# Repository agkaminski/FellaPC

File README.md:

# FellaPC

All-in-keyboard 6502 based PC with built-in BASIC interpreter.

Features:

- BASIC interpreter,
- 6502/65C02/W65C02S CPU @1.8432 MHz,
- 32 KiB of ROM, 24 KiB of static RAM,
- 640x480@60Hz VGA adapter with character generator (80x60 black and white text mode only),
- 6522 VIA for onboard control, I2C memory and user port,
- 2 UARTs (USB-C and RS-232),
- 68 or 63 button mechanical keyboard,
- edge connector expansion port,
- powered via USB-C port.

## Memory map

[Memory map](memmap.md)

## BASIC

FellaPC provides BASIC language subset (partially inspired by C64 BASIC).

### Program editing

Simple line editor is provided, code is entered line by line. To insert a new line or
overwrite existing line type in the line number followed by the code.

Example

```
10 FOR I = 0 TO 10
20 PRINT I
30 NEXT I
```

Let's say we want to change line number 20 to print a square of I insted. To do this
simply type in a new version of this line:

```
20 PRINT I*I
```

The program will be updated:

```
LIST

10 FOR I = 0 TO 10
20 PRINT I*I
30 NEXT I

Ready
```

### Commands

Following commands are supported:

#### PRINT

Print out to the screen.

Syntax examples:

```
PRINT "String"
PRINT "String", variable
PRINT "String"; variable
PRINT variable
PRINT var1, var2
```

#### INPUT

Prompt user for input, real numbers only.

Syntax examples:

```
INPUT var
INPUT "Prompt", var
```

#### FOR, TO, STEP, NEXT

Used for loops. Intelacing and infinite loop nesting are supported.

Syntax example:

```
10 FOR VAR=0 TO 10 STEP 2
20 PRINT I
30 NEXT I
```

Above loop will output:

```
0
2
4
6
8
```

#### GOTO

Jump to the line in the code.

Syntax example:

```
10 GOTO 30
20 PRINT "foo"
30 PRINT "bar"
```

Above code will output only `bar`, as `foo` has been skipped by `goto`.

#### GOSUB, RETURN

Similar to GOTO, but allows returning back from the destination of jump via `RETURN`.
Return address (line after `GOSUB`) is placed on the return stack. There is no limit
on the stack depth (apart from the computer memory capacity).

Syntax example:

```
10 GOSUB 200
20 PRINT "bar"
30 END
200 PRINT "foo"
210 RETURN
```

Folowing code will output:

```
foo
bar
```

#### IF, THEN, ELSE

Conditional execution.

Syntax example:

```
var = 5
10 IF var > 10 THEN 100 ELSE 200
100 PRINT "foo"
200 PRINT "bar"
```

Above code will only output `bar`, as var is not greater than 10.

#### CLEAR

Clear the screen and return cursor to the home position.

#### END

End program execution, return the interactive mode.

#### RUN

Starts execution of the program. Can be used in the interactive mode only.

#### LIST

Displays program. Can be used in the interactive mode only.

#### SAVE

Stores the program on the non-volatile memory. Can be used in the interactive mode only.

#### LOAD

Loads the program from the non-volatile memory. Can be used in the interactive mode only.

#### ABS()

Return absolute value.

Syntax example:

```
10 PRINT ABS(-5)
20 PRINT ABS(5)
```

This program will output:

```
5
5
```

#### FRE

Pseudo-variable. Return available BASIC memory in bytes.

#### INT()

Returns integer part of the real number.

Syntax example

```
PRINT INT(3.1412)
```

Will output `3`.

#### RND

Pseudo-variable. Return a random real number in the range of <0, 1).

#### PEEK(), POKE()

Functions that allow direct reading and modification of the computer memory.

Syntax examples:

```
PRINT PEEK(100)
```

Displays value of the memory at address 100.

```
POKE(100, 42)
```

Stores 42 at the address 100.

#### Operators

Following operators are supported:

```
( ) * + , - / ; < = > <= >= AND NOT OR
```

#### Variables

Variables are declared on the first use:

```
a = 5
var = 42
```

## Limitations

Applies to rev A, rev B:

All limitations in the firmware come from the limited size of the ROM space and
poor performance of the CC65 C compiler. 16 KB of program memory was thought to be
just enought to fit a full BASIC interpreter implementation. Alas, CC65 does not optimize
almost at all for the code size. 6502 is also infamous of not playing nice with the
C language. There was much struggle at the end of the development with the ROM space
running out - so some features were removed or abandoned and some functions has been
rewritten in assembled instead (which provides huge savings). It was deciced against
writing the BASIC interpreter itself in the assembler, in hope to reuse it in the future
project, with its portability in mind. Writing the whole firmware in assembler would also
prolong the project and more it difficult to maintain.

Due to above concerns, following hardware features are not handled by the firmware:

- both UARTs,
- 6522 VIA (apart from I2C and VGA ROM selection),
- interrupts (only NMI/VBLANK is handled).

Although these features can still be used by PEEK and POKE keywords of BASIC.

Visual glitches are expected on the VGA output when the VRAM is being modified. CPU is
too slow and DRAM refresh takes too long to be able to perfom any operation during
VBLANK.

## PCB

FellaPC rev C SBC PCB and keyboard PCB are a 2-layer design.

## Case

Case is provided as STL files that are designed for the FDM 3D priting. There are
three parts:

- keyboard,
- main body,
- bottom panel.

All parts are too big to be printed in one piece on most 3D printers, so cutting
the model during slicing and glueing back together after printing might be needed.
Threaded inserts have to be embedded in the plastic.

Hardware needed:

- threaded inserts:
 - M3 4x5 mm 9 pieces,
 - M3 4x4 mm 4 pieces,
- bolts:
 - M3x4 or M3x5 for keyboard and SCB 8 pieces,
 - M3x25 for main body 5 pieces.

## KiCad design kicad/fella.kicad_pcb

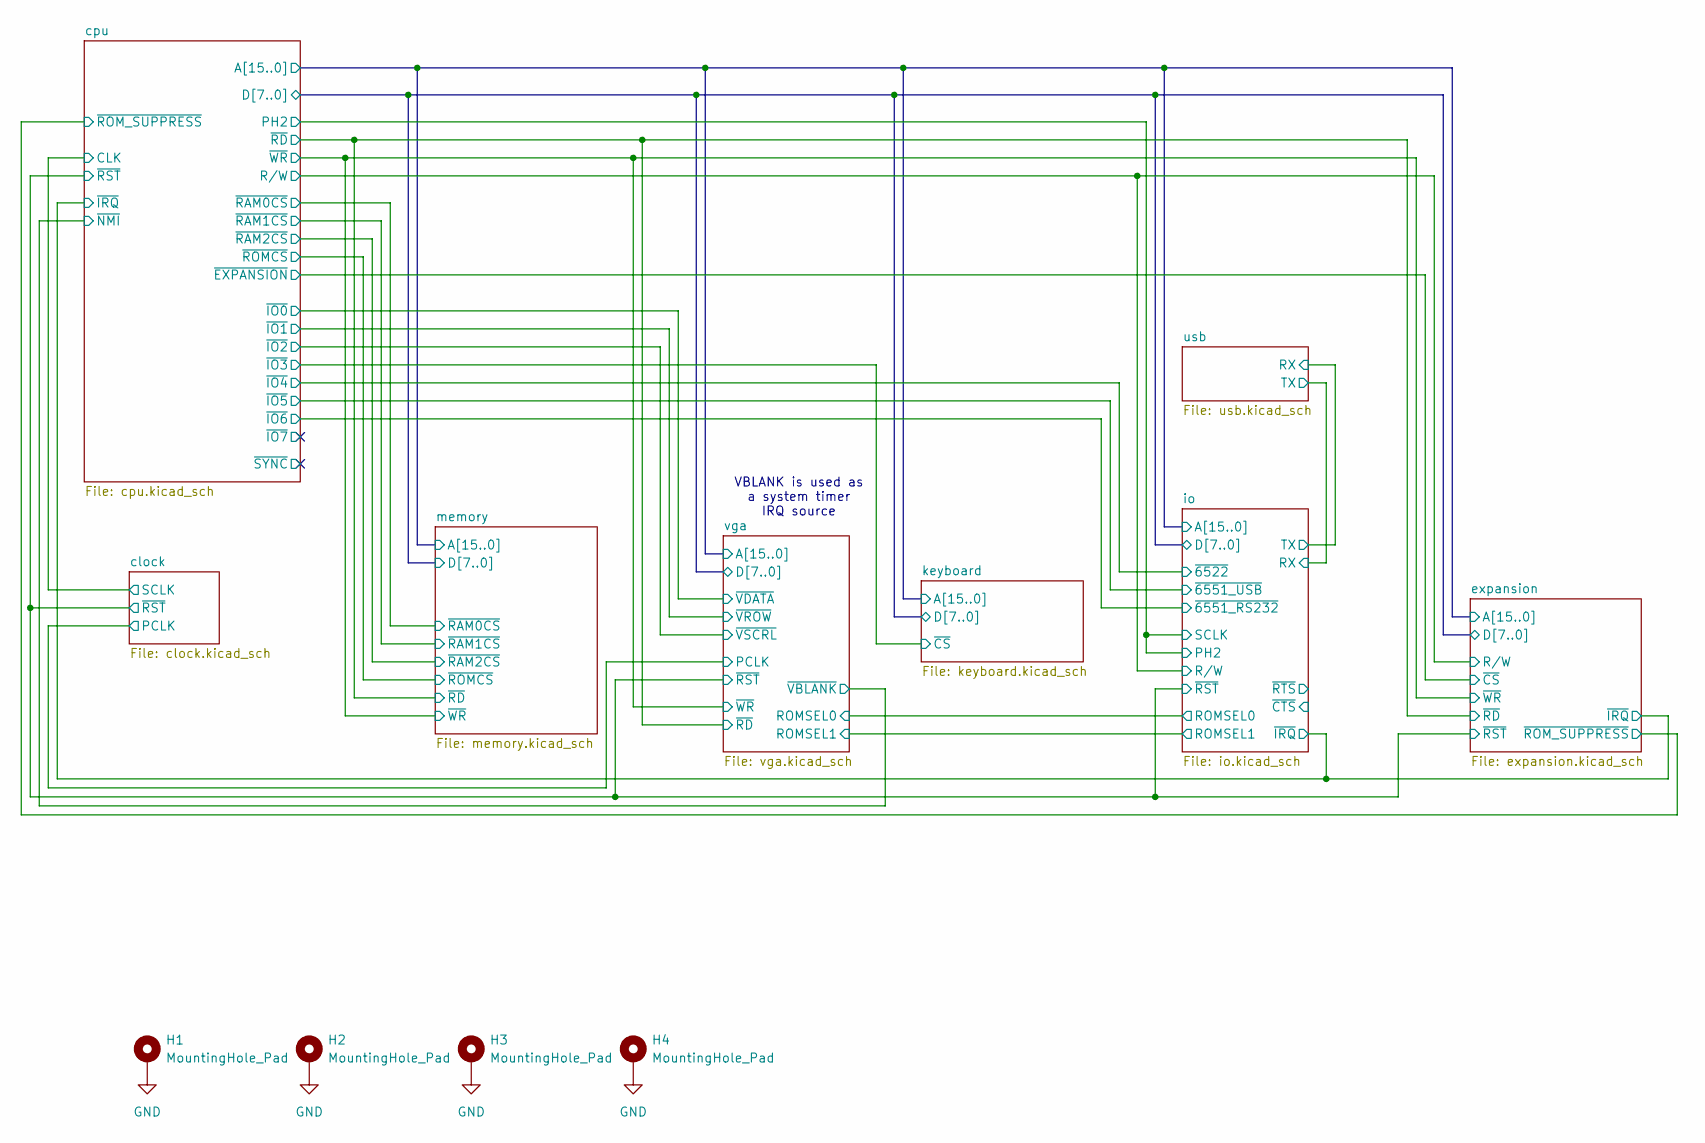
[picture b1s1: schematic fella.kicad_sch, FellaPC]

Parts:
H1, H2, H3, H4: MountingHole_Pad; MountingHole_3.2mm_M3_Pad_Via

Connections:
GND: H1.1, H2.1, H3.1, H4.1; also elsewhere on the board

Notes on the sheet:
VBLANK is used as a system timer IRQ source

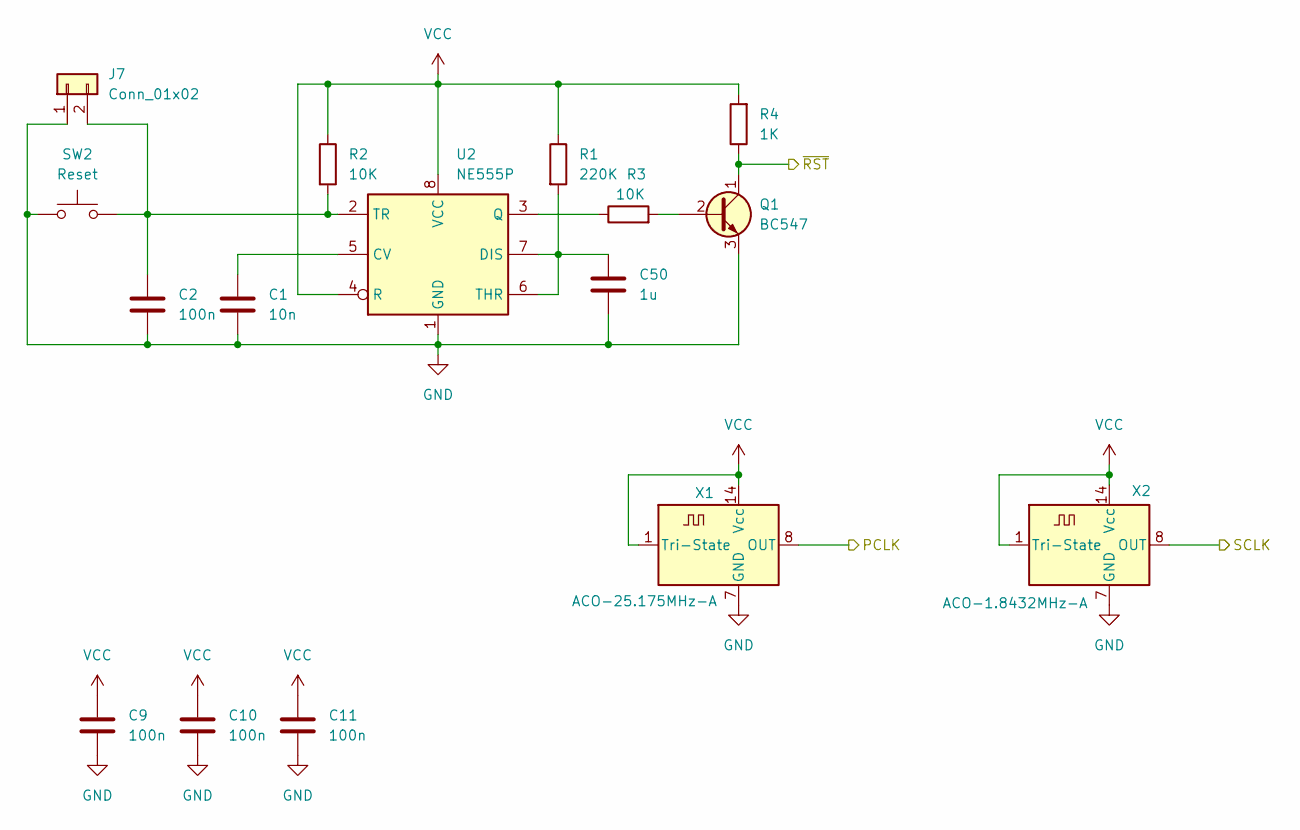
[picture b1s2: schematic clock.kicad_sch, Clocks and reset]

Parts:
C1: 10n; C_Disc_D5.0mm_W2.5mm_P2.50mm
C2, C9, C10, C11: 100n; C_Disc_D5.0mm_W2.5mm_P2.50mm
C50: 1u; C_Disc_D5.0mm_W2.5mm_P2.50mm
J7: Conn_01x02; PinHeader_1x02_P2.54mm_Vertical
Q1: BC547; TO-92
R1: 220K; R_Axial_DIN0207_L6.3mm_D2.5mm_P7.62mm_Horizontal
R2, R3: 10K; R_Axial_DIN0207_L6.3mm_D2.5mm_P7.62mm_Horizontal
R4: 1K; R_Axial_DIN0207_L6.3mm_D2.5mm_P7.62mm_Horizontal
SW2: Reset; SW_TH_Tactile_Omron_B3F-10xx
U2: NE555P; DIP-8_W7.62mm
X1: ACO-25.175MHz-A; Oscillator_DIP-14
X2: ACO-1.8432MHz-A; Oscillator_DIP-14

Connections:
/clock/PCLK: X1.8 (OUT); also elsewhere on the board
/clock/SCLK: X2.8 (OUT); also elsewhere on the board
/clock/~RST: Q1.1 (C), R4.1; also elsewhere on the board
GND: C1.2, C2.2, C9.2, C10.2, C11.2, C50.2, J7.1, Q1.3 (E), SW2.1, U2.1 (GND), X1.7 (GND), X2.7 (GND); also elsewhere on the board
unnamed: C2.1, J7.2, R2.2, SW2.2, U2.2 (TR)
unnamed: Q1.2 (B), R3.2
unnamed: C1.1, U2.5 (CV)
unnamed: C50.1, R1.2, U2.6 (THR), U2.7 (DIS)
unnamed: R3.1, U2.3 (Q)
VCC: C9.1, C10.1, C11.1, R1.1, R2.1, R4.2, U2.4 (R), U2.8 (VCC), X1.1 (Tri-State), X1.14 (Vcc), X2.1 (Tri-State), X2.14 (Vcc); also elsewhere on the board

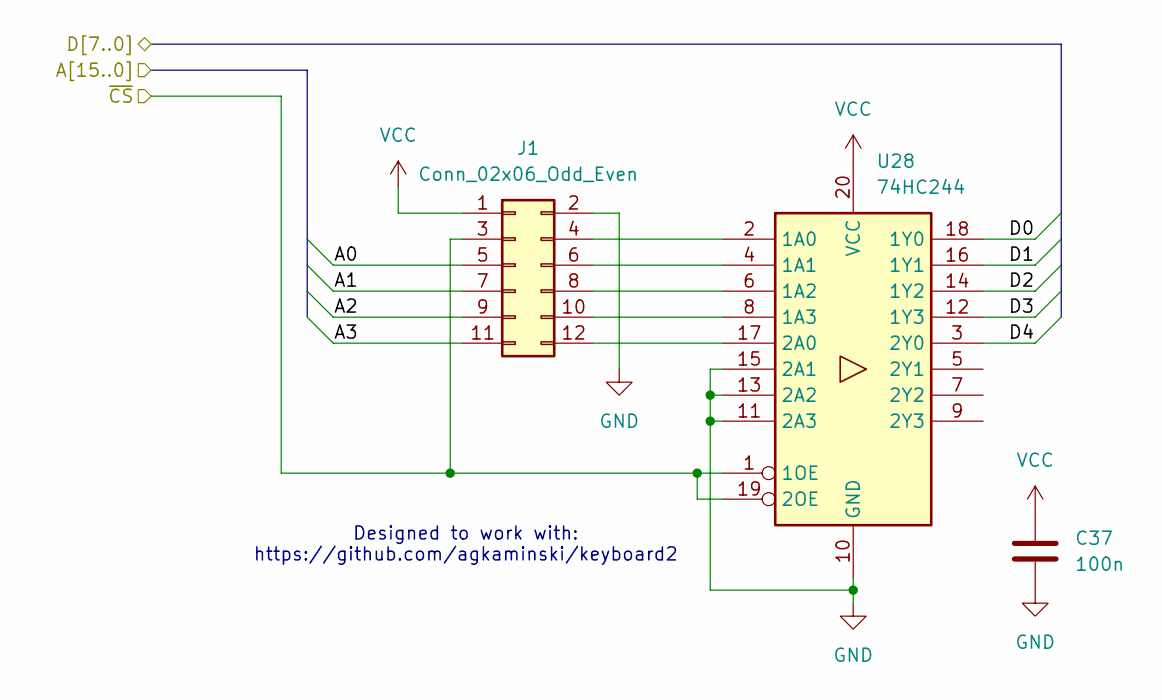
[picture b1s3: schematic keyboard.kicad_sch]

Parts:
C37: 100n; C_Disc_D5.0mm_W2.5mm_P2.50mm
J1: Conn_02x06_Odd_Even; IDC-Header_2x06_P2.54mm_Vertical
U28: 74HC244; DIP-20_W7.62mm

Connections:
/cpu/A0: J1.5; also elsewhere on the board
/cpu/A1: J1.7; also elsewhere on the board
/cpu/A2: J1.9; also elsewhere on the board
/cpu/A3: J1.11; also elsewhere on the board
/cpu/D0: U28.18 (1Y0); also elsewhere on the board
/cpu/D1: U28.16 (1Y1); also elsewhere on the board
/cpu/D2: U28.14 (1Y2); also elsewhere on the board
/cpu/D3: U28.12 (1Y3); also elsewhere on the board
/cpu/D4: U28.3 (2Y0); also elsewhere on the board
/cpu/~IO3: J1.3, U28.1 (1OE), U28.19 (2OE); also elsewhere on the board
GND: C37.2, J1.2, U28.10 (GND), U28.11 (2A3), U28.13 (2A2), U28.15 (2A1); also elsewhere on the board
unnamed: J1.4, U28.2 (1A0)
unnamed: J1.6, U28.4 (1A1)
unnamed: J1.8, U28.6 (1A2)
unnamed: J1.10, U28.8 (1A3)
unnamed: J1.12, U28.17 (2A0)
VCC: C37.1, J1.1, U28.20 (VCC); also elsewhere on the board

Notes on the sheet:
Designed to work with: https://github.com/agkaminski/keyboard2

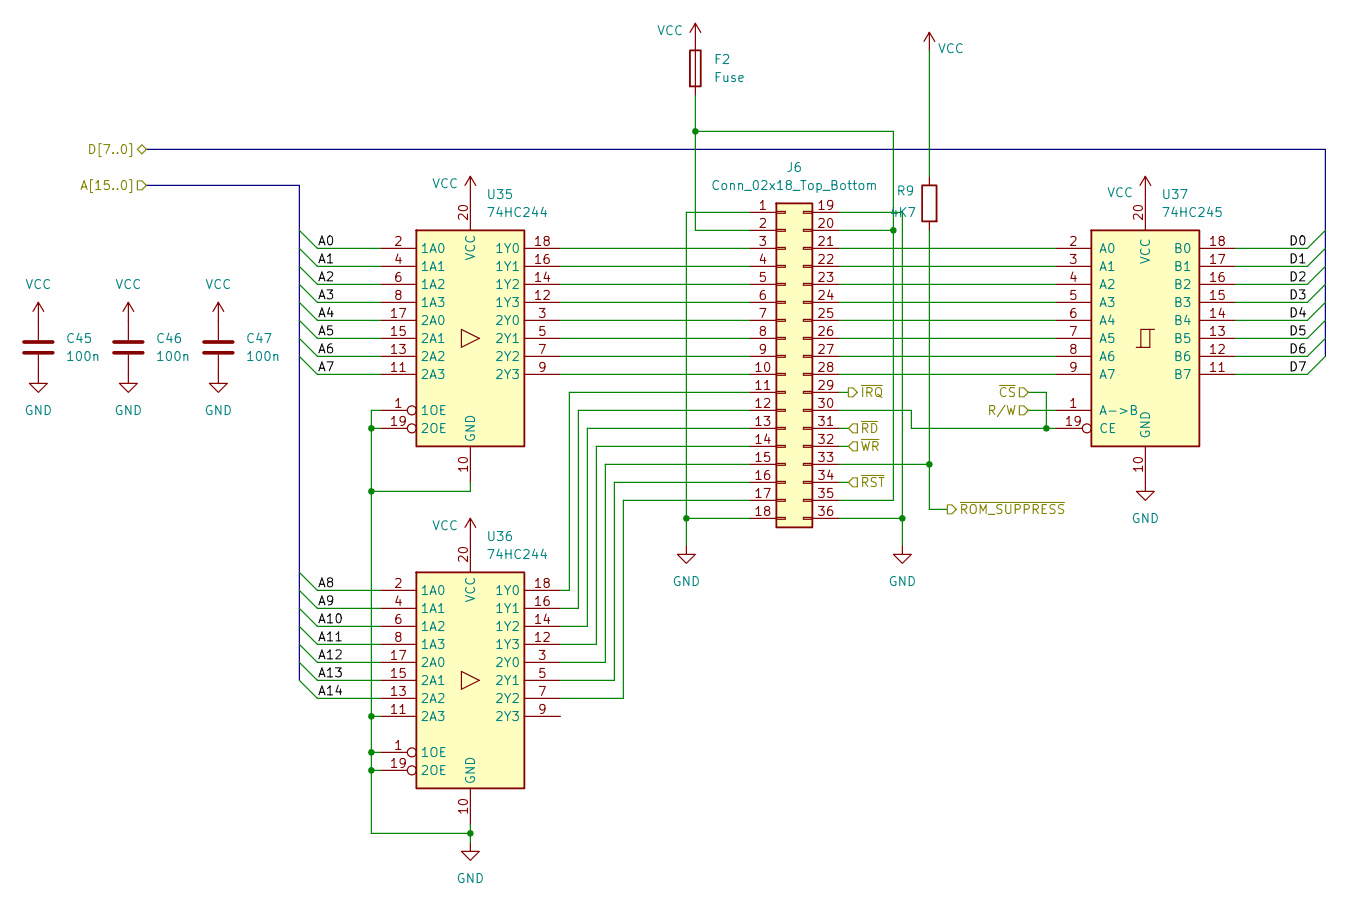
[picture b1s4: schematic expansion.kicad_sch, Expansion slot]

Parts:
C45, C46, C47: 100n; C_Disc_D5.0mm_W2.5mm_P2.50mm
F2: Fuse; Fuse_Littelfuse_395Series
J6: Conn_02x18_Top_Bottom; EDGE_2x18
R9: 4K7; R_Axial_DIN0207_L6.3mm_D2.5mm_P7.62mm_Horizontal
U35, U36: 74HC244; DIP-20_W7.62mm
U37: 74HC245; DIP-20_W7.62mm

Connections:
/clock/~RST: J6.34; also elsewhere on the board
/cpu/A0: U35.2 (1A0); also elsewhere on the board
/cpu/A1: U35.4 (1A1); also elsewhere on the board
/cpu/A2: U35.6 (1A2); also elsewhere on the board
/cpu/A3: U35.8 (1A3); also elsewhere on the board
/cpu/A4: U35.17 (2A0); also elsewhere on the board
/cpu/A5: U35.15 (2A1); also elsewhere on the board
/cpu/A6: U35.13 (2A2); also elsewhere on the board
/cpu/A7: U35.11 (2A3); also elsewhere on the board
/cpu/A8: U36.2 (1A0); also elsewhere on the board
/cpu/A9: U36.4 (1A1); also elsewhere on the board
/cpu/A10: U36.6 (1A2); also elsewhere on the board
/cpu/A11: U36.8 (1A3); also elsewhere on the board
/cpu/A12: U36.17 (2A0); also elsewhere on the board
/cpu/A13: U36.15 (2A1); also elsewhere on the board
/cpu/A14: U36.13 (2A2); also elsewhere on the board
/cpu/D0: U37.18 (B0); also elsewhere on the board
/cpu/D1: U37.17 (B1); also elsewhere on the board
/cpu/D2: U37.16 (B2); also elsewhere on the board
/cpu/D3: U37.15 (B3); also elsewhere on the board
/cpu/D4: U37.14 (B4); also elsewhere on the board
/cpu/D5: U37.13 (B5); also elsewhere on the board
/cpu/D6: U37.12 (B6); also elsewhere on the board
/cpu/D7: U37.11 (B7); also elsewhere on the board
/cpu/R/W: U37.1 (A->B); also elsewhere on the board
/cpu/~EXPANSION: J6.30, U37.19 (CE); also elsewhere on the board
/cpu/~IRQ: J6.29; also elsewhere on the board
/cpu/~RD: J6.31; also elsewhere on the board
/cpu/~ROM_SUPPRESS: J6.33, R9.2; also elsewhere on the board
/cpu/~WR: J6.32; also elsewhere on the board
GND: C45.2, C46.2, C47.2, J6.1, J6.18, J6.19, J6.36, U35.1 (1OE), U35.10 (GND), U35.19 (2OE), U36.1 (1OE), U36.10 (GND), U36.11 (2A3), U36.19 (2OE), U37.10 (GND); also elsewhere on the board
unnamed: F2.2, J6.2, J6.20, J6.35
unnamed: J6.3, U35.18 (1Y0)
unnamed: J6.4, U35.16 (1Y1)
unnamed: J6.5, U35.14 (1Y2)
unnamed: J6.6, U35.12 (1Y3)
unnamed: J6.7, U35.3 (2Y0)
unnamed: J6.8, U35.5 (2Y1)
unnamed: J6.9, U35.7 (2Y2)
unnamed: J6.10, U35.9 (2Y3)
unnamed: J6.11, U36.18 (1Y0)
unnamed: J6.12, U36.16 (1Y1)
unnamed: J6.13, U36.14 (1Y2)
unnamed: J6.14, U36.12 (1Y3)
unnamed: J6.15, U36.3 (2Y0)
unnamed: J6.16, U36.5 (2Y1)
unnamed: J6.17, U36.7 (2Y2)
unnamed: J6.21, U37.2 (A0)
unnamed: J6.22, U37.3 (A1)
unnamed: J6.23, U37.4 (A2)
unnamed: J6.24, U37.5 (A3)
unnamed: J6.25, U37.6 (A4)
unnamed: J6.26, U37.7 (A5)
unnamed: J6.27, U37.8 (A6)
unnamed: J6.28, U37.9 (A7)
VCC: C45.1, C46.1, C47.1, F2.1, R9.1, U35.20 (VCC), U36.20 (VCC), U37.20 (VCC); also elsewhere on the board

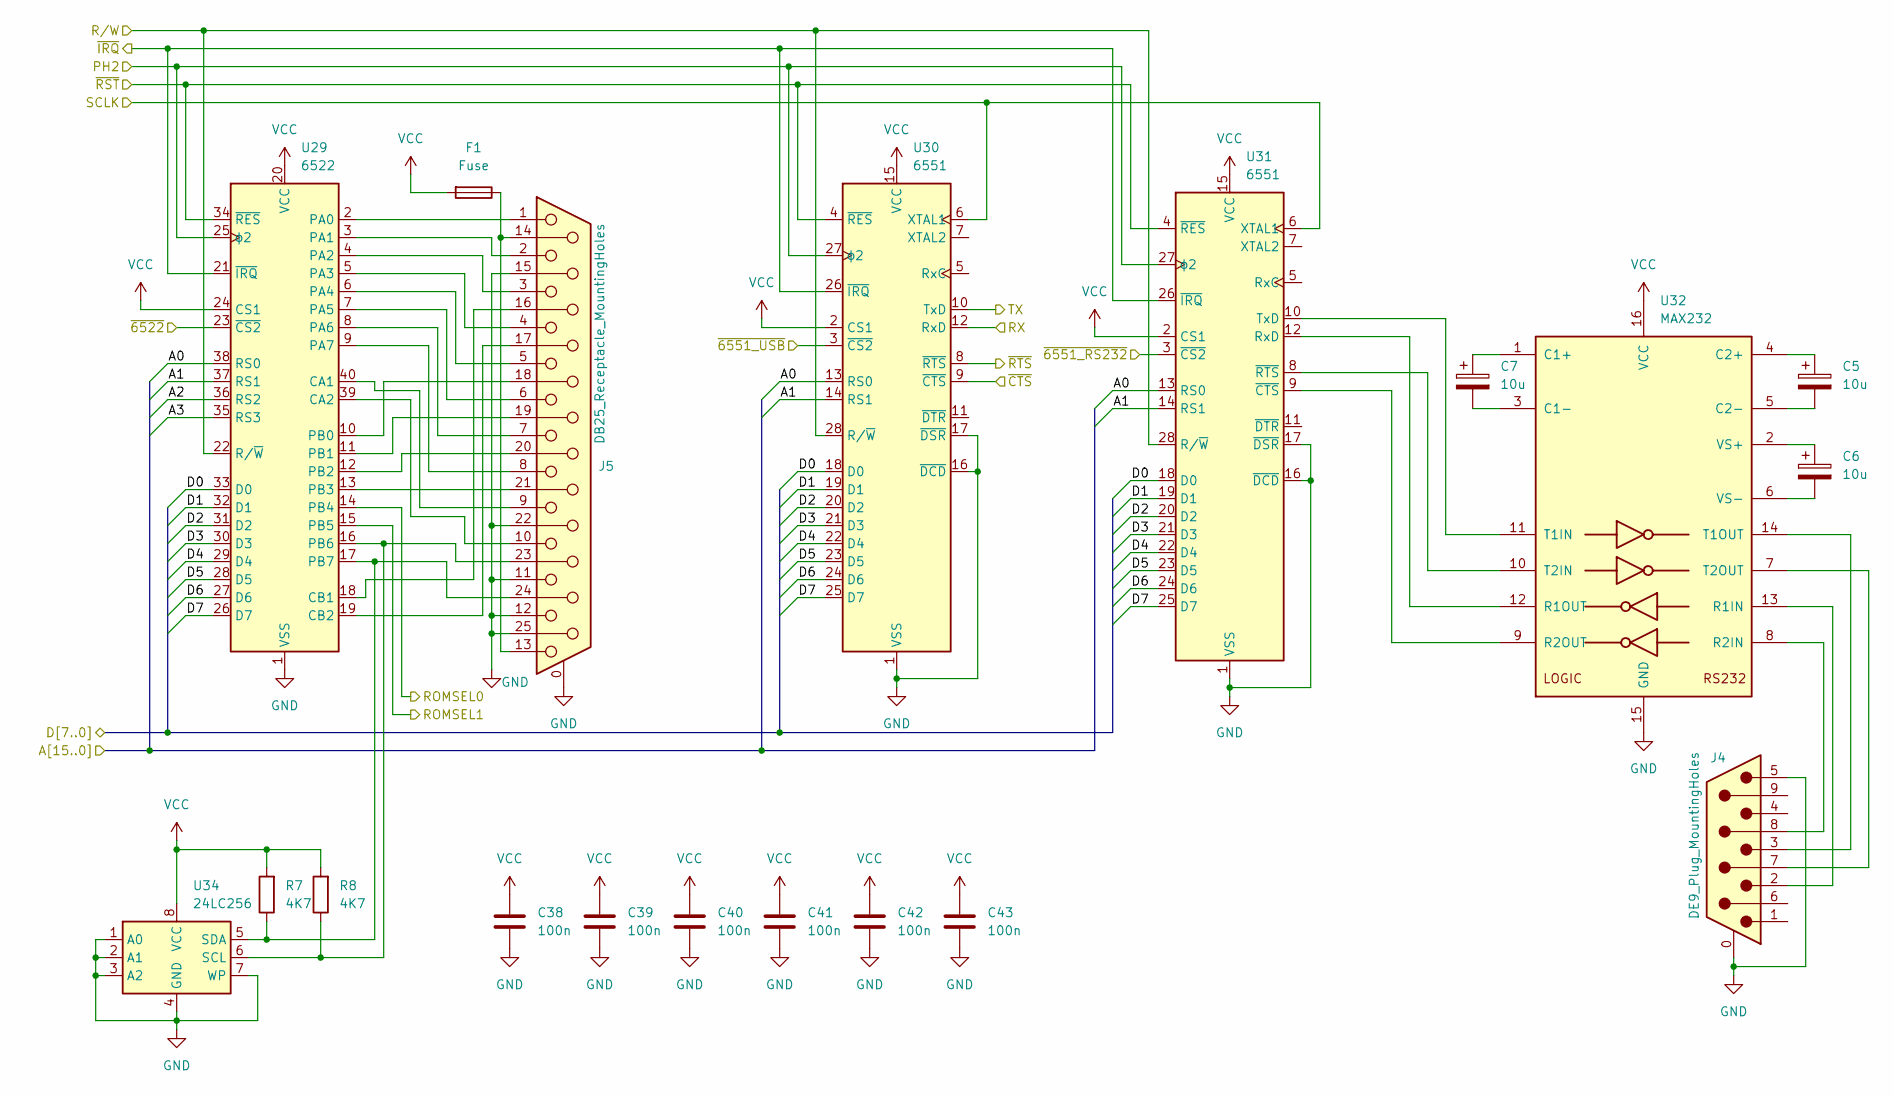
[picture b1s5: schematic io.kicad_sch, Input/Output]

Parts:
C5, C6, C7: 10u; CP_Radial_D6.3mm_P2.50mm
C38, C39, C40, C41, C42, C43: 100n; C_Disc_D5.0mm_W2.5mm_P2.50mm
F1: Fuse; Fuse_Littelfuse_395Series
J4: DE9_Plug_MountingHoles; DSUB-9_Male_Horizontal_P2.77x2.84mm_EdgePinOffset7.70mm_Hou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
J5: DB25_Receptacle_MountingHoles; DSUB-25_Socket_Horizontal_P2.77x2.84mm_EdgePinOffset7.70mm_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
R7, R8: 4K7; R_Axial_DIN0207_L6.3mm_D2.5mm_P7.62mm_Horizontal
U29: 6522; DIP-40_W15.24mm
U30, U31: 6551; DIP-28_W15.24mm
U32: MAX232; DIP-16_W7.62mm
U34: 24LC256; DIP-8_W7.62mm

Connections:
/clock/SCLK: U29.25 (ϕ2), U30.6 (XTAL1), U30.27 (ϕ2), U31.6 (XTAL1), U31.27 (ϕ2); also elsewhere on the board
/clock/~RST: U29.34 (~RES), U30.4 (~RES), U31.4 (~RES); also elsewhere on the board
/cpu/A0: U29.38 (RS0), U30.13 (RS0), U31.13 (RS0); also elsewhere on the board
/cpu/A1: U29.37 (RS1), U30.14 (RS1), U31.14 (RS1); also elsewhere on the board
/cpu/A2: U29.36 (RS2); also elsewhere on the board
/cpu/A3: U29.35 (RS3); also elsewhere on the board
/cpu/D0: U29.33 (D0), U30.18 (D0), U31.18 (D0); also elsewhere on the board
/cpu/D1: U29.32 (D1), U30.19 (D1), U31.19 (D1); also elsewhere on the board
/cpu/D2: U29.31 (D2), U30.20 (D2), U31.20 (D2); also elsewhere on the board
/cpu/D3: U29.30 (D3), U30.21 (D3), U31.21 (D3); also elsewhere on the board
/cpu/D4: U29.29 (D4), U30.22 (D4), U31.22 (D4); also elsewhere on the board
/cpu/D5: U29.28 (D5), U30.23 (D5), U31.23 (D5); also elsewhere on the board
/cpu/D6: U29.27 (D6), U30.24 (D6), U31.24 (D6); also elsewhere on the board
/cpu/D7: U29.26 (D7), U30.25 (D7), U31.25 (D7); also elsewhere on the board
/cpu/R/W: U29.22 (R/~W), U30.28 (R/~W), U31.28 (R/~W); also elsewhere on the board
/cpu/~IO4: U29.23 (~CS2); also elsewhere on the board
/cpu/~IO5: U30.3 (~CS2); also elsewhere on the board
/cpu/~IO6: U31.3 (~CS2); also elsewhere on the board
/cpu/~IRQ: U29.21 (~IRQ), U30.26 (~IRQ), U31.26 (~IRQ); also elsewhere on the board
/io/ROMSEL0: U29.14 (PB4); also elsewhere on the board
/io/ROMSEL1: U29.15 (PB5); also elsewhere on the board
/io/RX: U30.12 (RxD); also elsewhere on the board
/io/TX: U30.10 (TxD); also elsewhere on the board
/io/~CTS: U30.9 (~CTS)
/io/~RTS: U30.8 (~RTS)
GND: C38.2, C39.2, C40.2, C41.2, C42.2, C43.2, J4.0 (PAD), J4.5, J5.0 (PAD), J5.11, J5.12, J5.15, J5.22, J5.25, U29.1 (VSS), U30.1 (VSS), U30.16 (~DCD), U30.17 (~DSR), U31.1 (VSS), U31.16 (~DCD), U31.17 (~DSR), U32.15 (GND), U34.1 (A0), U34.2 (A1), U34.3 (A2), U34.4 (GND), U34.7 (WP); also elsewhere on the board
unnamed: F1.1, J5.13, J5.14
unnamed: J5.16, U29.18 (CB1)
unnamed: J5.17, U29.19 (CB2)
unnamed: J5.18, U29.10 (PB0)
unnamed: J5.19, U29.11 (PB1)
unnamed: J5.20, U29.12 (PB2)
unnamed: J5.21, U29.13 (PB3)
unnamed: J5.23, R8.1, U29.16 (PB6), U34.6 (SCL)
unnamed: J5.24, R7.1, U29.17 (PB7), U34.5 (SDA)
unnamed: J5.9, U29.40 (CA1)
unnamed: J5.10, U29.39 (CA2)
unnamed: J5.1, U29.2 (PA0)
unnamed: J5.2, U29.3 (PA1)
unnamed: J5.3, U29.4 (PA2)
unnamed: J5.4, U29.5 (PA3)
unnamed: J5.5, U29.6 (PA4)
unnamed: J5.6, U29.7 (PA5)
unnamed: J5.7, U29.8 (PA6)
unnamed: J5.8, U29.9 (PA7)
unnamed: U31.12 (RxD), U32.12 (R1OUT)
unnamed: U31.10 (TxD), U32.11 (T1IN)
unnamed: U31.9 (~CTS), U32.9 (R2OUT)
unnamed: U31.8 (~RTS), U32.10 (T2IN)
unnamed: C7.1, U32.1 (C1+)
unnamed: C7.2, U32.3 (C1-)
unnamed: C5.1, U32.4 (C2+)
unnamed: C5.2, U32.5 (C2-)
unnamed: J4.2, U32.13 (R1IN)
unnamed: J4.8, U32.8 (R2IN)
unnamed: J4.3, U32.14 (T1OUT)
unnamed: J4.7, U32.7 (T2OUT)
unnamed: C6.1, U32.2 (VS+)
unnamed: C6.2, U32.6 (VS-)
VCC: C38.1, C39.1, C40.1, C41.1, C42.1, C43.1, F1.2, R7.2, R8.2, U29.20 (VCC), U29.24 (CS1), U30.2 (CS1), U30.15 (VCC), U31.2 (CS1), U31.15 (VCC), U32.16 (VCC), U34.8 (VCC); also elsewhere on the board

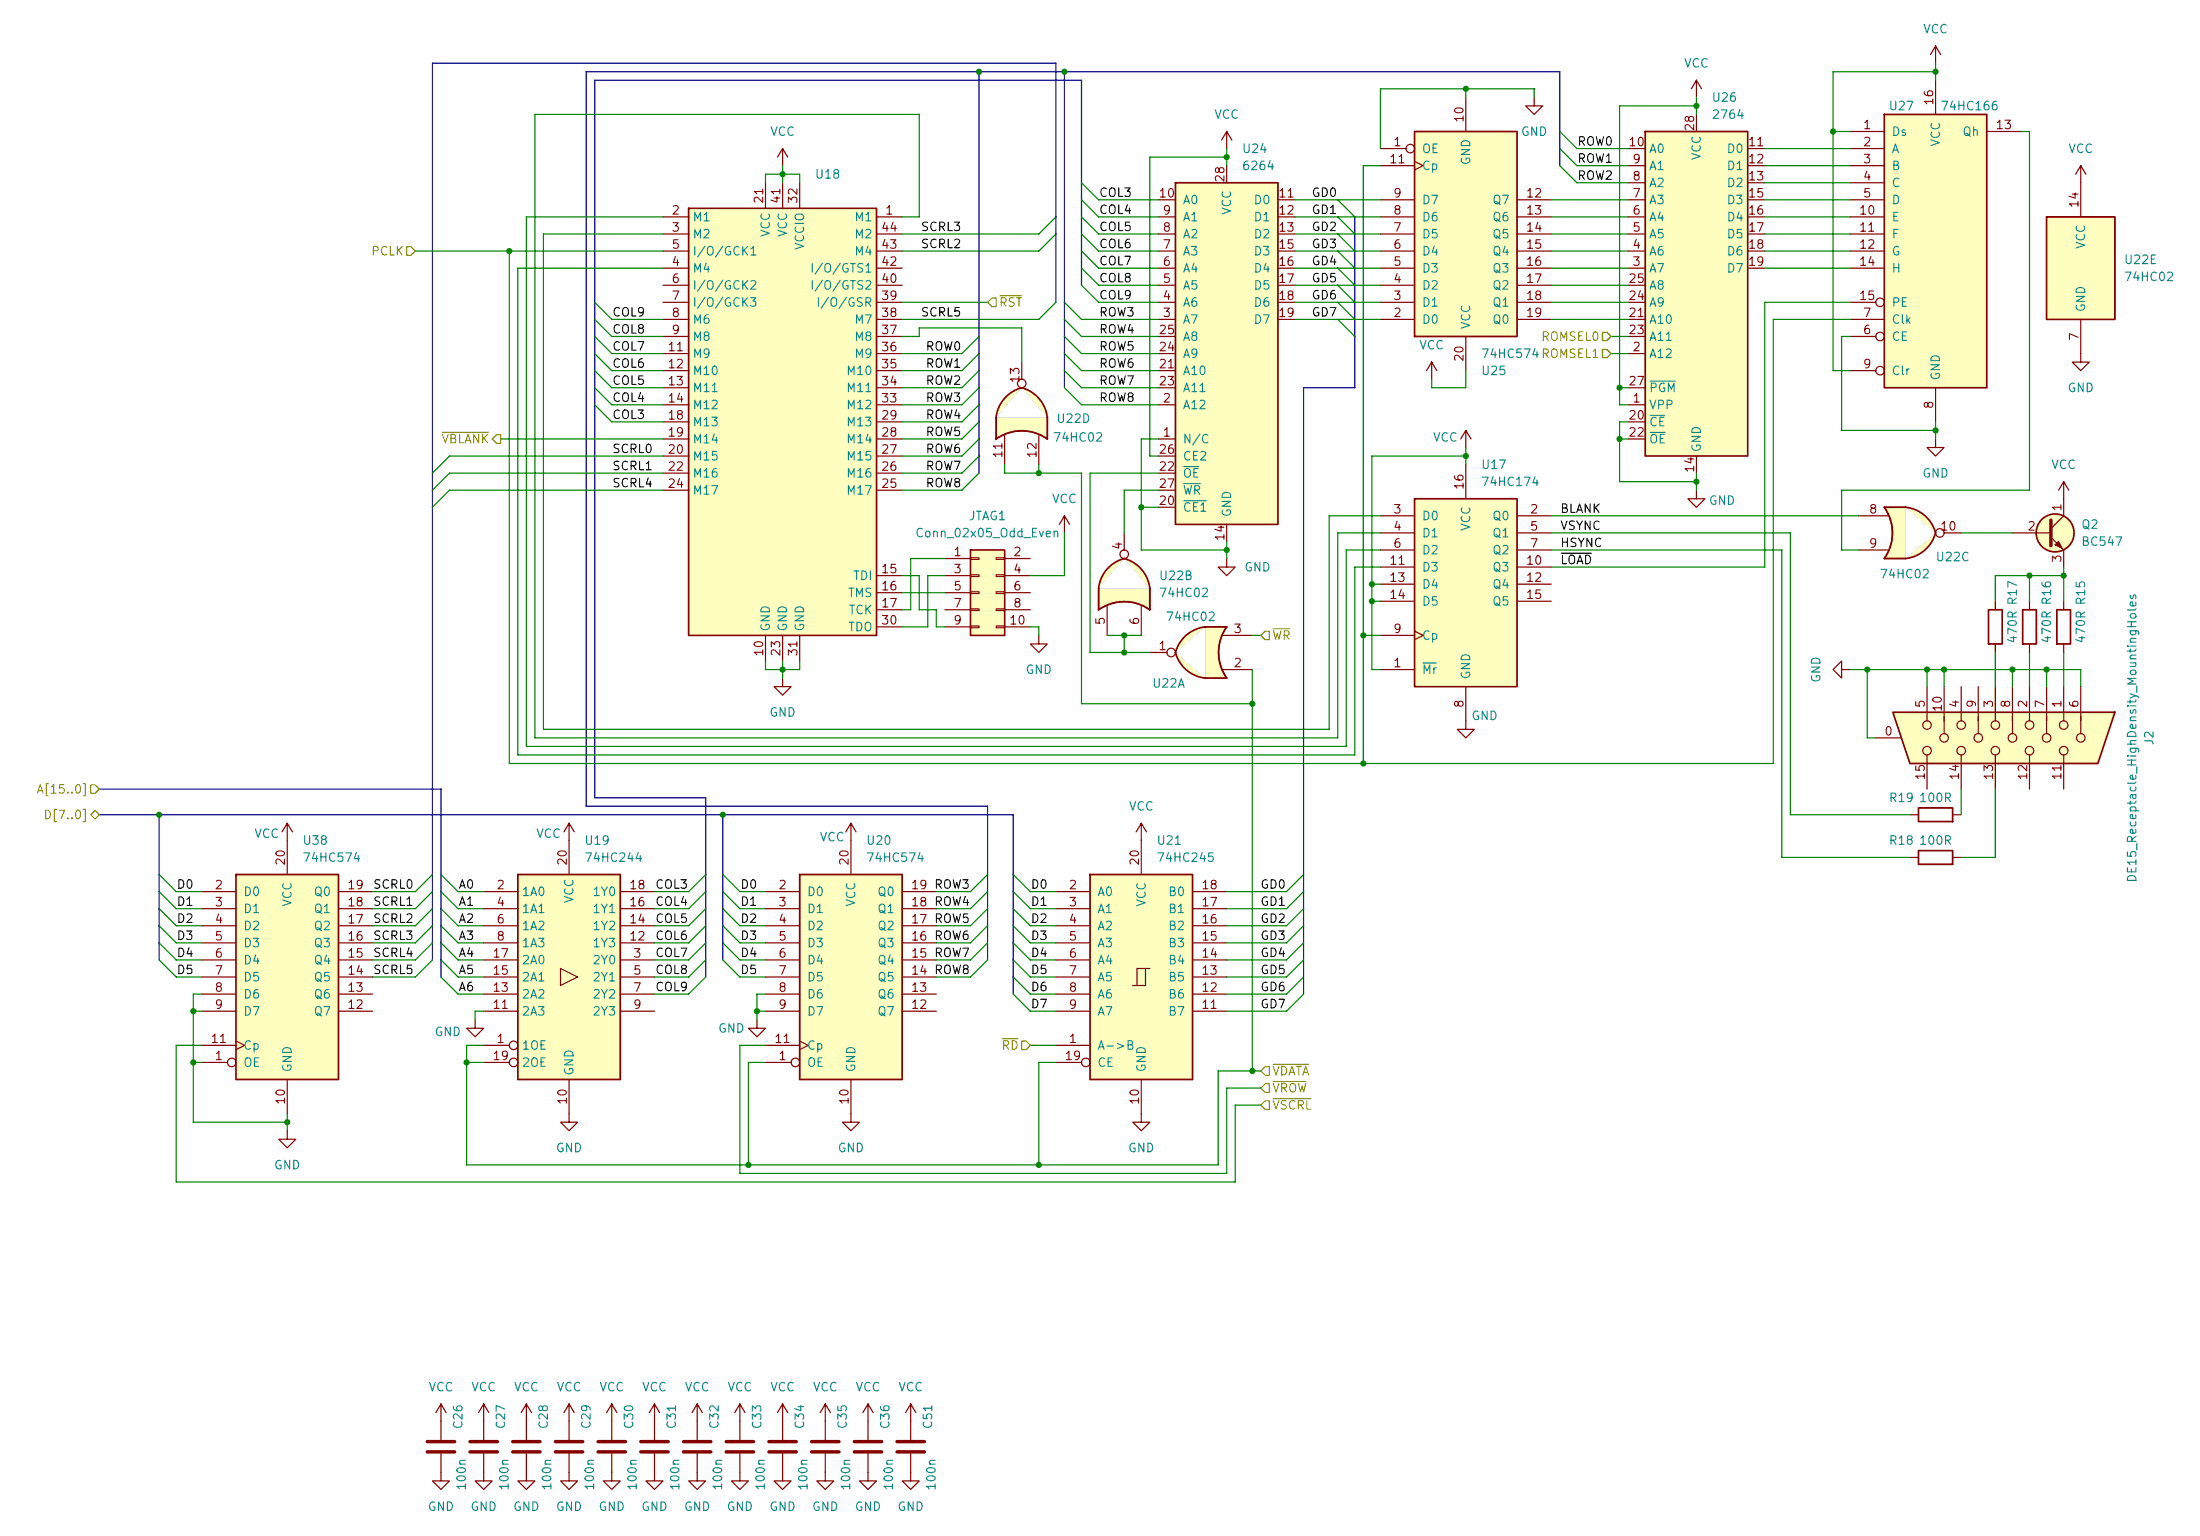
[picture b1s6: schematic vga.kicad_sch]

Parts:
C26, C27, C28, C29, C30, C31, C32, C33, C34, C35, C36, C51: 100n; C_Disc_D5.0mm_W2.5mm_P2.50mm
J2: DE15_Receptacle_HighDensity_MountingHoles; DSUB-15-HD_Female_Horizontal_P2.29x1.98mm_EdgePinOffset3.03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
JTAG1: Conn_02x05_Odd_Even; IDC-Header_2x05_P2.54mm_Vertical
Q2: BC547; TO-92
R15, R16, R17: 470R; R_Axial_DIN0207_L6.3mm_D2.5mm_P7.62mm_Horizontal
R18, R19: 100R; R_Axial_DIN0207_L6.3mm_D2.5mm_P7.62mm_Horizontal
U17: 74HC174; DIP-16_W7.62mm
U18: XC9536PC44; PLCC-44_THT-Socket
U19: 74HC244; DIP-20_W7.62mm
U20, U25, U38: 74HC574; DIP-20_W7.62mm
U21: 74HC245; DIP-20_W7.62mm
U22: 74HC02; DIP-14_W7.62mm
U24: 6264; DIP-28_W15.24mm
U26: 2764; DIP-28_W15.24mm
U27: 74HC166; DIP-16_W7.62mm

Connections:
/clock/PCLK: U17.9 (Cp), U18.5 (I/O/GCK1), U25.11 (Cp), U27.7 (Clk); also elsewhere on the board
/clock/~RST: U18.39 (I/O/GSR); also elsewhere on the board
/cpu/A0: U19.2 (1A0); also elsewhere on the board
/cpu/A1: U19.4 (1A1); also elsewhere on the board
/cpu/A2: U19.6 (1A2); also elsewhere on the board
/cpu/A3: U19.8 (1A3); also elsewhere on the board
/cpu/A4: U19.17 (2A0); also elsewhere on the board
/cpu/A5: U19.15 (2A1); also elsewhere on the board
/cpu/A6: U19.13 (2A2); also elsewhere on the board
/cpu/D0: U20.2 (D0), U21.2 (A0), U38.2 (D0); also elsewhere on the board
/cpu/D1: U20.3 (D1), U21.3 (A1), U38.3 (D1); also elsewhere on the board
/cpu/D2: U20.4 (D2), U21.4 (A2), U38.4 (D2); also elsewhere on the board
/cpu/D3: U20.5 (D3), U21.5 (A3), U38.5 (D3); also elsewhere on the board
/cpu/D4: U20.6 (D4), U21.6 (A4), U38.6 (D4); also elsewhere on the board
/cpu/D5: U20.7 (D5), U21.7 (A5), U38.7 (D5); also elsewhere on the board
/cpu/D6: U21.8 (A6); also elsewhere on the board
/cpu/D7: U21.9 (A7); also elsewhere on the board
/cpu/~IO0: U19.1 (1OE), U19.19 (2OE), U20.1 (OE), U21.19 (CE), U22.2, U22.11, U22.12; also elsewhere on the board
/cpu/~IO1: U20.11 (Cp); also elsewhere on the board
/cpu/~IO2: U38.11 (Cp); also elsewhere on the board
/cpu/~NMI: U18.19 (M14); also elsewhere on the board
/cpu/~RD: U21.1 (A->B); also elsewhere on the board
/cpu/~WR: U22.3; also elsewhere on the board
/io/ROMSEL0: U26.23 (A11); also elsewhere on the board
/io/ROMSEL1: U26.2 (A12); also elsewhere on the board
/vga/BLANK: U17.2 (Q0), U22.8
/vga/COL3: U18.18 (M13), U19.18 (1Y0), U24.10 (A0)
/vga/COL4: U18.14 (M12), U19.16 (1Y1), U24.9 (A1)
/vga/COL5: U18.13 (M11), U19.14 (1Y2), U24.8 (A2)
/vga/COL6: U18.12 (M10), U19.12 (1Y3), U24.7 (A3)
/vga/COL7: U18.11 (M9), U19.3 (2Y0), U24.6 (A4)
/vga/COL8: U18.9 (M8), U19.5 (2Y1), U24.5 (A5)
/vga/COL9: U18.8 (M6), U19.7 (2Y2), U24.4 (A6)
/vga/GD0: U21.18 (B0), U24.11 (D0), U25.9 (D7)
/vga/GD1: U21.17 (B1), U24.12 (D1), U25.8 (D6)
/vga/GD2: U21.16 (B2), U24.13 (D2), U25.7 (D5)
/vga/GD3: U21.15 (B3), U24.15 (D3), U25.6 (D4)
/vga/GD4: U21.14 (B4), U24.16 (D4), U25.5 (D3)
/vga/GD5: U21.13 (B5), U24.17 (D5), U25.4 (D2)
/vga/GD6: U21.12 (B6), U24.18 (D6), U25.3 (D1)
/vga/GD7: U21.11 (B7), U24.19 (D7), U25.2 (D0)
/vga/HSYNC: R18.1, U17.7 (Q2)
/vga/ROW0: U18.36 (M9), U26.10 (A0)
/vga/ROW1: U18.35 (M10), U26.9 (A1)
/vga/ROW2: U18.34 (M11), U26.8 (A2)
/vga/ROW3: U18.33 (M12), U20.19 (Q0), U24.3 (A7)
/vga/ROW4: U18.29 (M13), U20.18 (Q1), U24.25 (A8)
/vga/ROW5: U18.28 (M14), U20.17 (Q2), U24.24 (A9)
/vga/ROW6: U18.27 (M15), U20.16 (Q3), U24.21 (A10)
/vga/ROW7: U18.26 (M16), U20.15 (Q4), U24.23 (A11)
/vga/ROW8: U18.25 (M17), U20.14 (Q5), U24.2 (A12)
/vga/SCRL0: U18.20 (M15), U38.19 (Q0)
/vga/SCRL1: U18.22 (M16), U38.18 (Q1)
/vga/SCRL2: U18.43 (M4), U38.17 (Q2)
/vga/SCRL3: U18.44 (M2), U38.16 (Q3)
/vga/SCRL4: U18.24 (M17), U38.15 (Q4)
/vga/SCRL5: U18.38 (M7), U38.14 (Q5)
/vga/VSYNC: R19.1, U17.5 (Q1)
/vga/~LOAD: U17.10 (Q3), U27.15 (PE)
GND: C26.2, C27.2, C28.2, C29.2, C30.2, C31.2, C32.2, C33.2, C34.2, C35.2, C36.2, C51.2, J2.0, J2.5, J2.6, J2.7, J2.8, J2.10, JTAG1.10, U17.8 (GND), U18.10 (GND), U18.23 (GND), U18.31 (GND), U19.10 (GND), U19.11 (2A3), U20.8 (D6), U20.9 (D7), U20.10 (GND), U21.10 (GND), U22.7 (GND), U24.1 (N/C), U24.14 (GND), U24.20 (~CE1), U25.1 (OE), U25.10 (GND), U26.14 (GND), U26.20 (~CE), U26.22 (~OE), U27.6 (CE), U27.8 (GND), U38.1 (OE), U38.8 (D6), U38.9 (D7), U38.10 (GND); also elsewhere on the board
unnamed: J2.1, R15.2
unnamed: J2.2, R16.2
unnamed: J2.3, R17.2
unnamed: J2.13, R18.2
unnamed: J2.14, R19.2
unnamed: JTAG1.1, U18.17 (TCK)
unnamed: JTAG1.3, U18.30 (TDO)
unnamed: JTAG1.5, U18.16 (TMS)
unnamed: JTAG1.9, U18.15 (TDI)
unnamed: Q2.2 (B), U22.10
unnamed: Q2.3 (E), R15.1, R16.1, R17.1
unnamed: U17.3 (D0), U18.3 (M2)
unnamed: U17.4 (D1), U18.1 (M1)
unnamed: U17.6 (D2), U18.2 (M1)
unnamed: U17.11 (D3), U18.4 (M4)
unnamed: U18.37 (M8), U22.13
unnamed: U22.1, U22.5, U22.6, U24.22 (~OE)
unnamed: U22.4, U24.27 (~WR)
unnamed: U25.19 (Q0), U26.21 (A10)
unnamed: U25.18 (Q1), U26.24 (A9)
unnamed: U25.17 (Q2), U26.25 (A8)
unnamed: U25.16 (Q3), U26.3 (A7)
unnamed: U25.15 (Q4), U26.4 (A6)
unnamed: U25.14 (Q5), U26.5 (A5)
unnamed: U25.13 (Q6), U26.6 (A4)
unnamed: U25.12 (Q7), U26.7 (A3)
unnamed: U26.11 (D0), U27.2 (A)
unnamed: U26.12 (D1), U27.3 (B)
unnamed: U26.13 (D2), U27.4 (C)
unnamed: U26.15 (D3), U27.5 (D)
unnamed: U26.16 (D4), U27.10 (E)
unnamed: U26.17 (D5), U27.11 (F)
unnamed: U26.18 (D6), U27.12 (G)
unnamed: U26.19 (D7), U27.14 (H)
unnamed: U22.9, U27.13 (Qh)
VCC: C26.1, C27.1, C28.1, C29.1, C30.1, C31.1, C32.1, C33.1, C34.1, C35.1, C36.1, C51.1, JTAG1.4, Q2.1 (C), U17.1 (~Mr), U17.13 (D4), U17.14 (D5), U17.16 (VCC), U18.21 (VCC), U18.32 (VCCIO), U18.41 (VCC), U19.20 (VCC), U20.20 (VCC), U21.20 (VCC), U22.14 (VCC), U24.26 (CE2), U24.28 (VCC), U25.20 (VCC), U26.1 (VPP), U26.27 (~PGM), U26.28 (VCC), U27.1 (Ds), U27.9 (Clr), U27.16 (VCC), U38.20 (VCC); also elsewhere on the board
